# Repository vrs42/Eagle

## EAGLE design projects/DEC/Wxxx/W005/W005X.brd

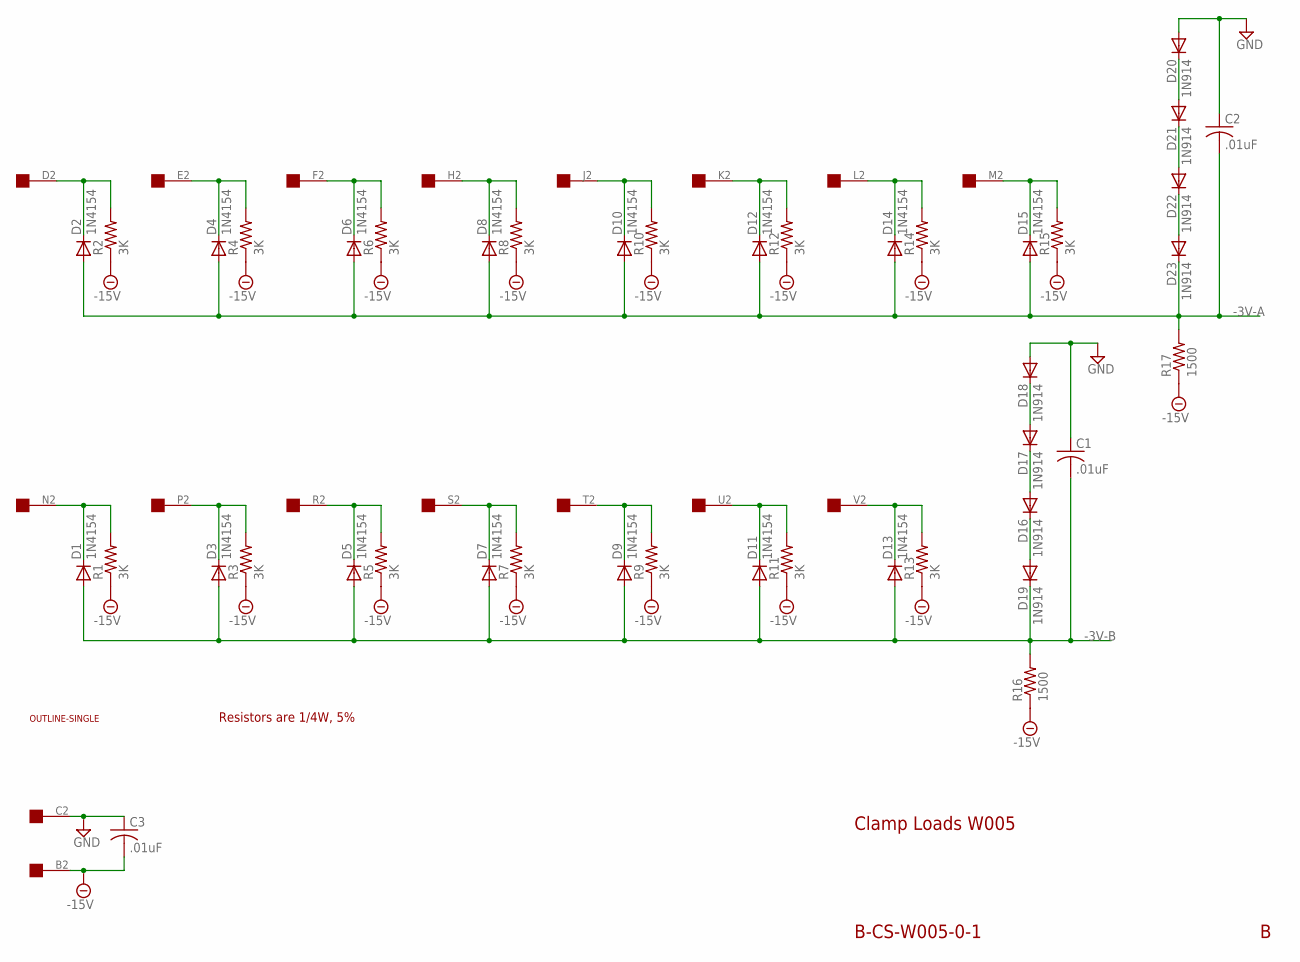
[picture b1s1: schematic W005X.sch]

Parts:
C1, C2, C3: .01uF; C050-025X075
D1, D2, D3, D4, D5, D6, D7, D8, D9, D10, D11, D12, D13, D14, D15: 1N4154; DO35-10
D16, D17, D18, D19, D20, D21, D22, D23: 1N914; DO35-10
R1, R2, R3, R4, R5, R6, R7, R8, R9, R10, R11, R12, R13, R14, R15: 3K; 0207/10
R16, R17: 1500; 0207/10
U$1: OUTLINE-SINGLE; SINGLE
U$2: EDGE-1; EDGE-CON1

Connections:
-3V-A: C2.2, D2.A, D4.A, D6.A, D8.A, D10.A, D12.A, D14.A, D15.A, D23.C, R17.2
-3V-B: C1.2, D1.A, D3.A, D5.A, D7.A, D9.A, D11.A, D13.A, D19.C, R16.2
-15V: C3.2, R1.1, R2.1, R3.1, R4.1, R5.1, R6.1, R7.1, R8.1, R9.1, R10.1, R11.1, R12.1, R13.1, R14.1, R15.1, R16.1, R17.1, U$2.B2
GND: C1.1, C2.1, C3.1, D18.A, D20.A, U$2.C2
unnamed: D22.C, D23.A
unnamed: D2.C, R2.2, U$2.D2
unnamed: D4.C, R4.2, U$2.E2
unnamed: D1.C, R1.2, U$2.N2
unnamed: D3.C, R3.2, U$2.P2
unnamed: D5.C, R5.2, U$2.R2
unnamed: D6.C, R6.2, U$2.F2
unnamed: D7.C, R7.2, U$2.S2
unnamed: D8.C, R8.2, U$2.H2
unnamed: D9.C, R9.2, U$2.T2
unnamed: D10.C, R10.2, U$2.J2
unnamed: D11.C, R11.2, U$2.U2
unnamed: D12.C, R12.2, U$2.K2
unnamed: D13.C, R13.2, U$2.V2
unnamed: D14.C, R14.2, U$2.L2
unnamed: D15.C, R15.2, U$2.M2
unnamed: D17.A, D18.C
unnamed: D16.A, D17.C
unnamed: D16.C, D19.A
unnamed: D20.C, D21.A
unnamed: D21.C, D22.A

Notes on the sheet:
Clamp Loads W005
B-CS-W005-0-1
Resistors are 1/4W, 5%

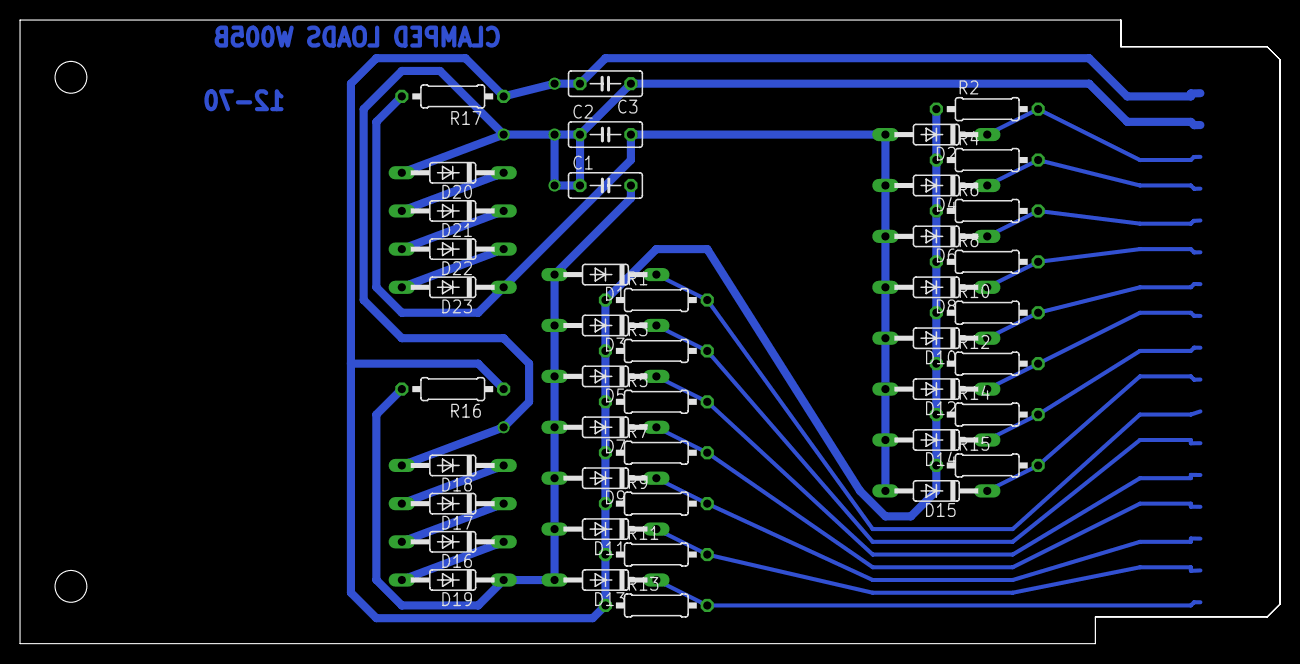
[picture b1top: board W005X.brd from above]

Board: 2 copper layers, 125.7 x 62.2 mm, 45 parts (0 on the bottom side), 25 nets.

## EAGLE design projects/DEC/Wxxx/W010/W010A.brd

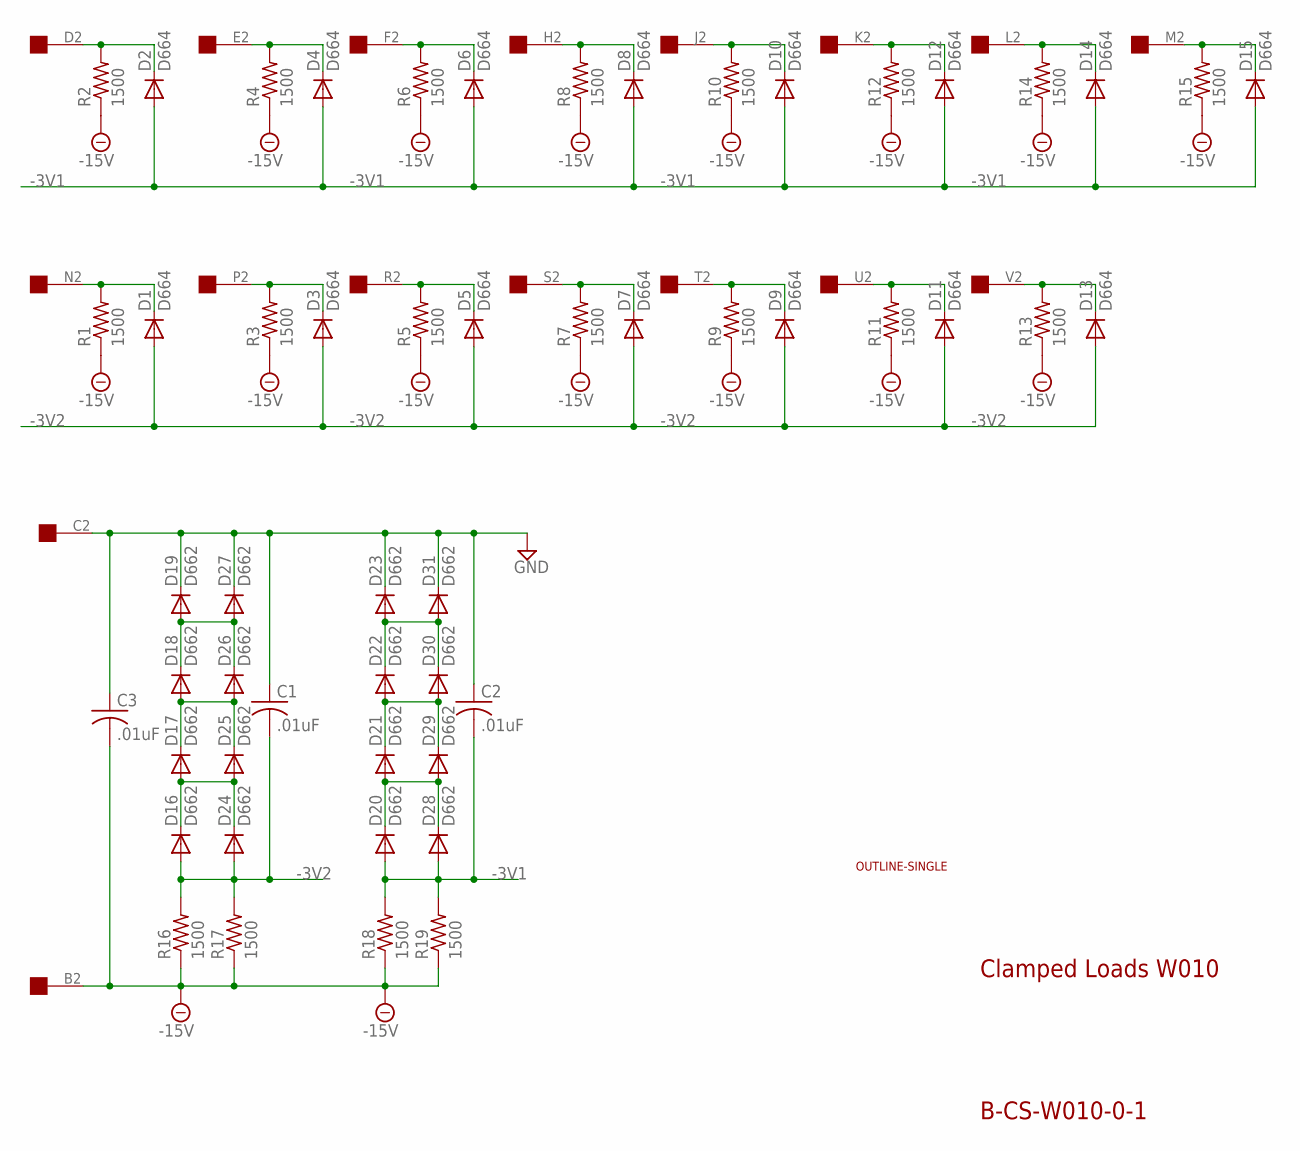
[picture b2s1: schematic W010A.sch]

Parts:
C1, C2, C3: .01uF; C063-025X075
D1, D2, D3, D4, D5, D6, D7, D8, D9, D10, D11, D12, D13, D14, D15: D664; DO35-10
D16, D17, D18, D19, D20, D21, D22, D23, D24, D25, D26, D27, D28, D29, D30, D31: D662; DO35-10
R1, R2, R3, R4, R5, R6, R7, R8, R9, R10, R11, R12, R13, R14, R15, R16, R17, R18, R19: 1500; 0207/10
U$1: EDGE-1; EDGE-CON1
U$2: OUTLINE-SINGLE; SINGLE

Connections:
-3V1: C2.2, D2.A, D4.A, D6.A, D8.A, D10.A, D12.A, D14.A, D15.A, D20.A, D28.A, R18.2, R19.2
-3V2: C1.2, D1.A, D3.A, D5.A, D7.A, D9.A, D11.A, D13.A, D16.A, D24.A, R16.2, R17.2
-15V: C3.2, R1.1, R2.1, R3.1, R4.1, R5.1, R6.1, R7.1, R8.1, R9.1, R10.1, R11.1, R12.1, R13.1, R14.1, R15.1, R16.1, R17.1, R18.1, R19.1, U$1.B2
GND: C1.1, C2.1, C3.1, D19.C, D23.C, D27.C, D31.C, U$1.C2
unnamed: D2.C, R2.2, U$1.D2
unnamed: D4.C, R4.2, U$1.E2
unnamed: D6.C, R6.2, U$1.F2
unnamed: D8.C, R8.2, U$1.H2
unnamed: D10.C, R10.2, U$1.J2
unnamed: D12.C, R12.2, U$1.K2
unnamed: D14.C, R14.2, U$1.L2
unnamed: D15.C, R15.2, U$1.M2
unnamed: D1.C, R1.2, U$1.N2
unnamed: D3.C, R3.2, U$1.P2
unnamed: D5.C, R5.2, U$1.R2
unnamed: D7.C, R7.2, U$1.S2
unnamed: D9.C, R9.2, U$1.T2
unnamed: D11.C, R11.2, U$1.U2
unnamed: D13.C, R13.2, U$1.V2
unnamed: D16.C, D17.A, D24.C, D25.A
unnamed: D17.C, D18.A, D25.C, D26.A
unnamed: D18.C, D19.A, D26.C, D27.A
unnamed: D20.C, D21.A, D28.C, D29.A
unnamed: D21.C, D22.A, D29.C, D30.A
unnamed: D22.C, D23.A, D30.C, D31.A

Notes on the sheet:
Clamped Loads W010
B-CS-W010-0-1

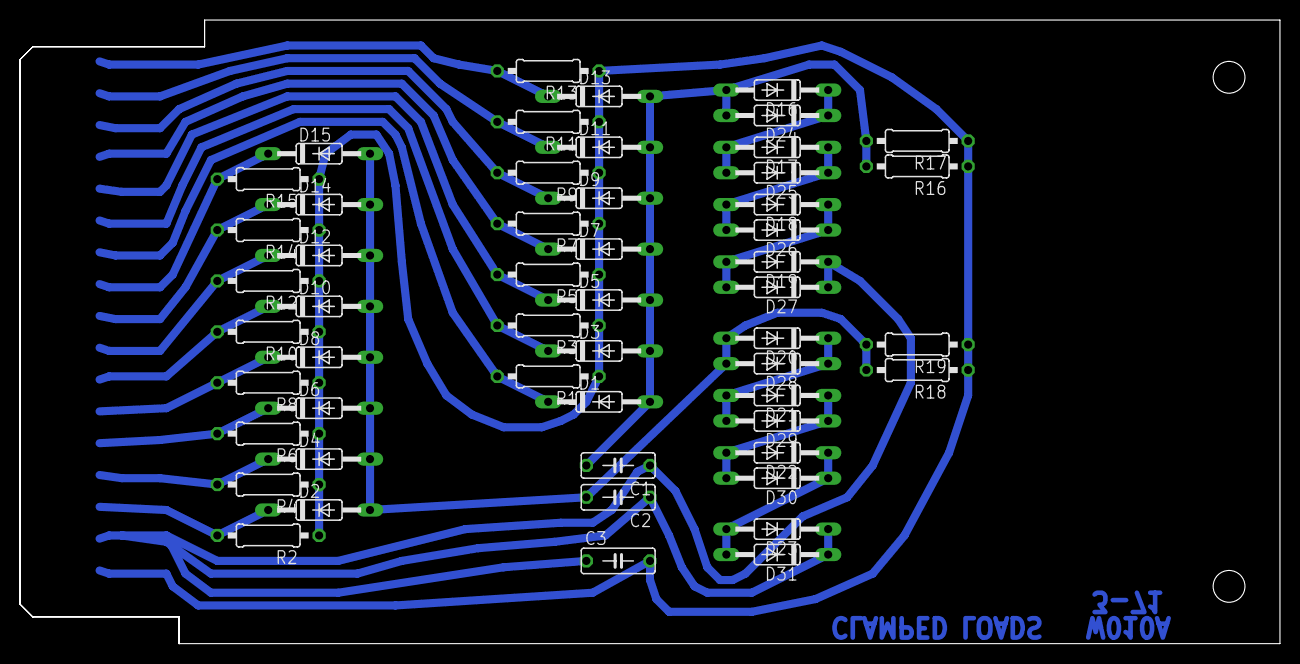
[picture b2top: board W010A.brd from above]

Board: 2 copper layers, 125.7 x 62.2 mm, 55 parts (0 on the bottom side), 25 nets.

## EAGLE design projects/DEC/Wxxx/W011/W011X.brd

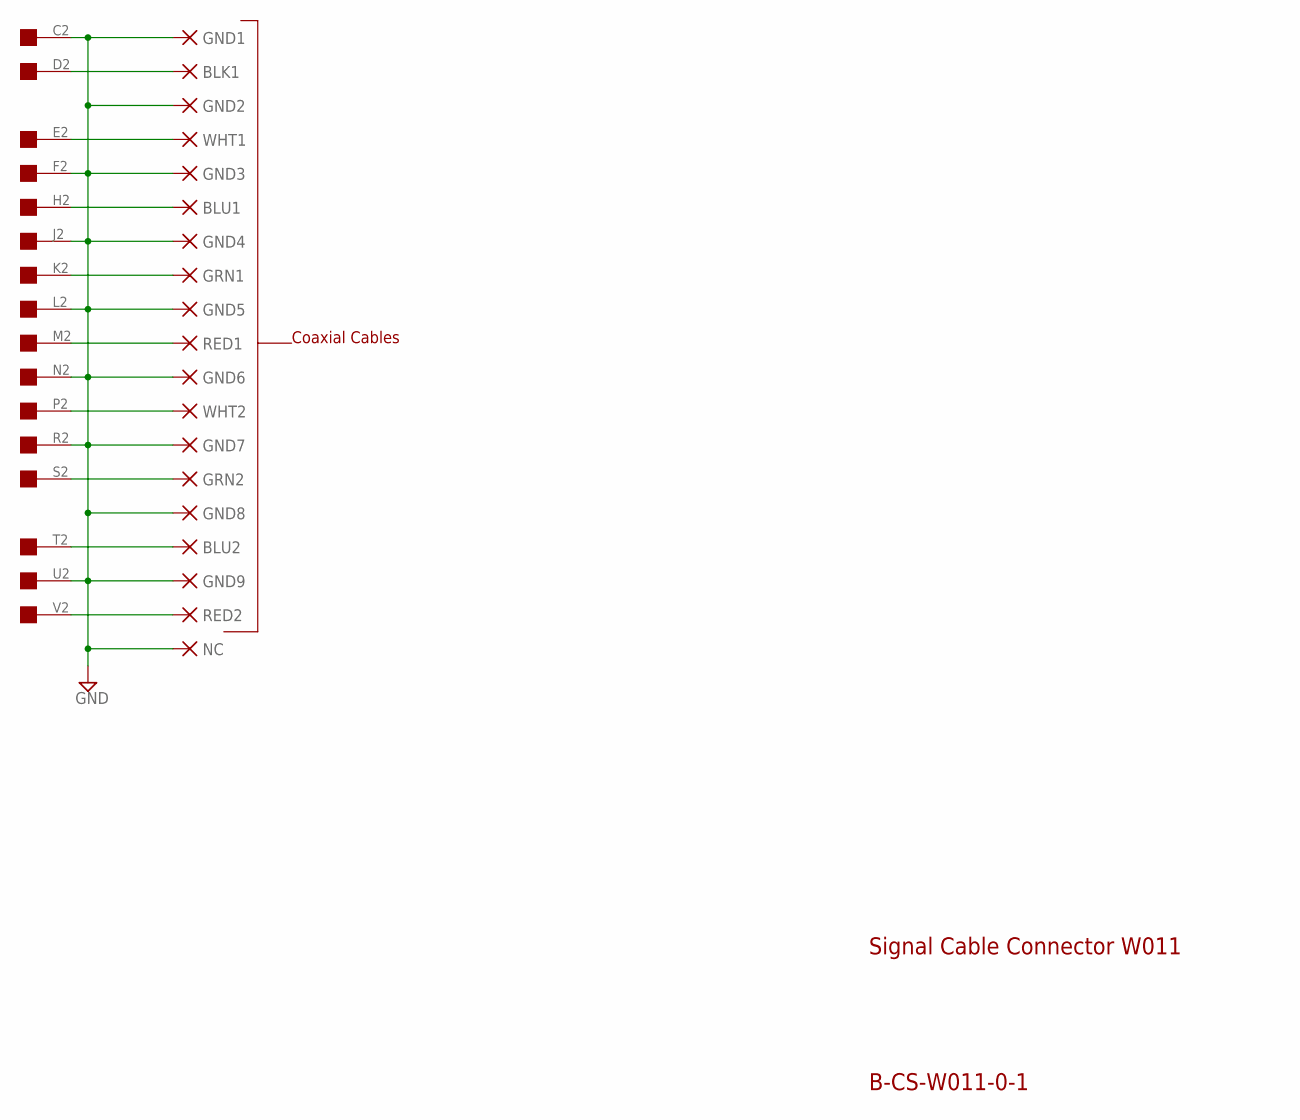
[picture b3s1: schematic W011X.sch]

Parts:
BLK1: PAD-0465; 0465
BLU1, BLU2: PAD-0465; 0465
GND1, GND2, GND3, GND4, GND5, GND6, GND7, GND8, GND9: PAD-0465; 0465
GRN1, GRN2: PAD-0465; 0465
NC: PAD-0465; 0465
RED1, RED2: PAD-0465; 0465
U$2: EDGE-1; EDGE-CON1
WHT1, WHT2: PAD-0465; 0465

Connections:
GND: GND1.P$1, GND2.P$1, GND3.P$1, GND4.P$1, GND5.P$1, GND6.P$1, GND7.P$1, GND8.P$1, GND9.P$1, NC.P$1, U$2.C2, U$2.F2, U$2.J2, U$2.L2, U$2.N2, U$2.R2, U$2.U2
unnamed: U$2.E2, WHT1.P$1
unnamed: BLU1.P$1, U$2.H2
unnamed: GRN1.P$1, U$2.K2
unnamed: RED1.P$1, U$2.M2
unnamed: U$2.P2, WHT2.P$1
unnamed: GRN2.P$1, U$2.S2
unnamed: BLU2.P$1, U$2.T2
unnamed: RED2.P$1, U$2.V2
unnamed: BLK1.P$1, U$2.D2

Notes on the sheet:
Signal Cable Connector W011
B-CS-W011-0-1
Coaxial Cables

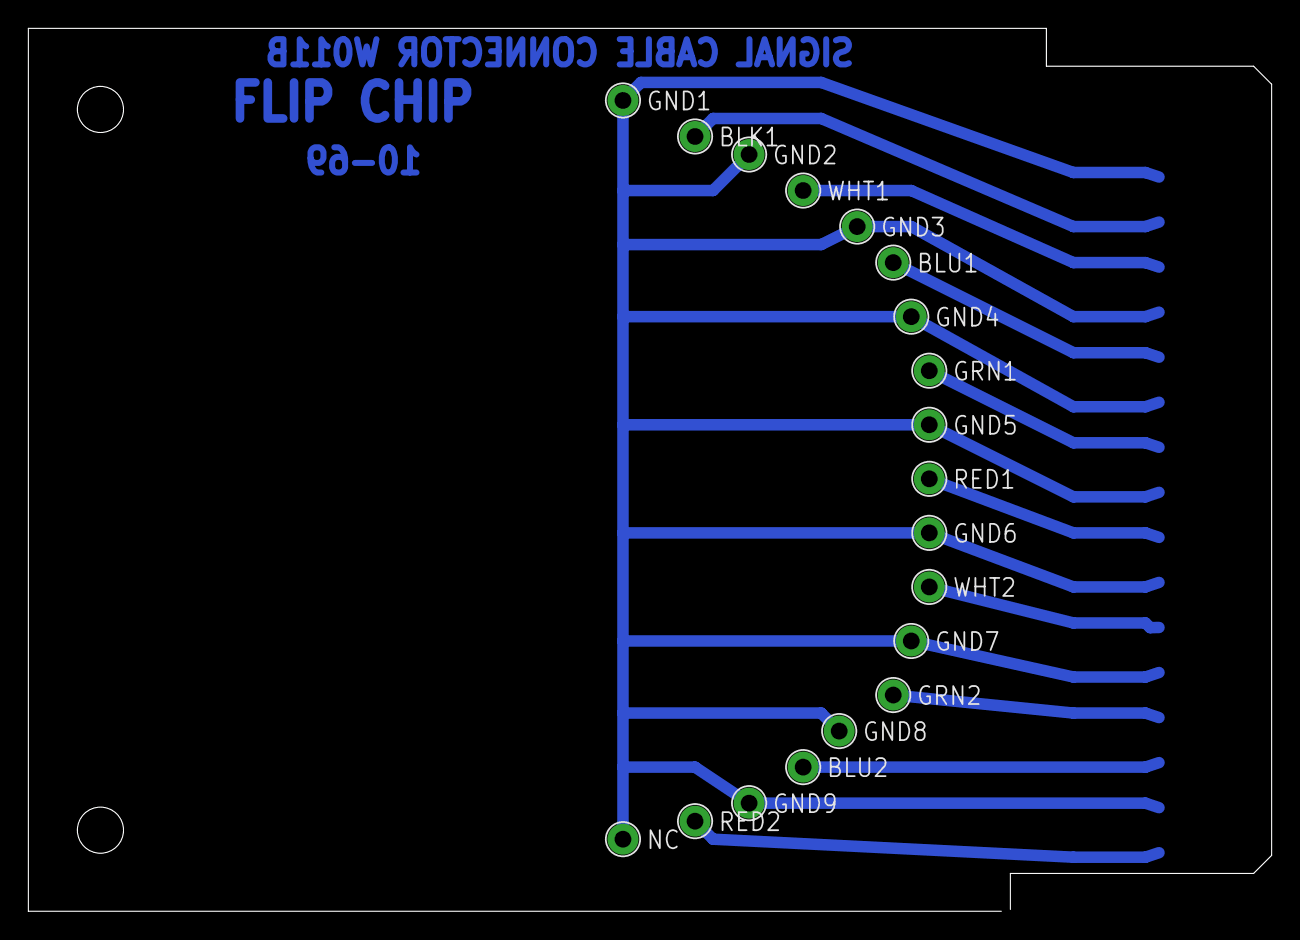
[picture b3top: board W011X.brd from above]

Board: 2 copper layers, 87.6 x 62.2 mm, 20 parts (0 on the bottom side), 10 nets.

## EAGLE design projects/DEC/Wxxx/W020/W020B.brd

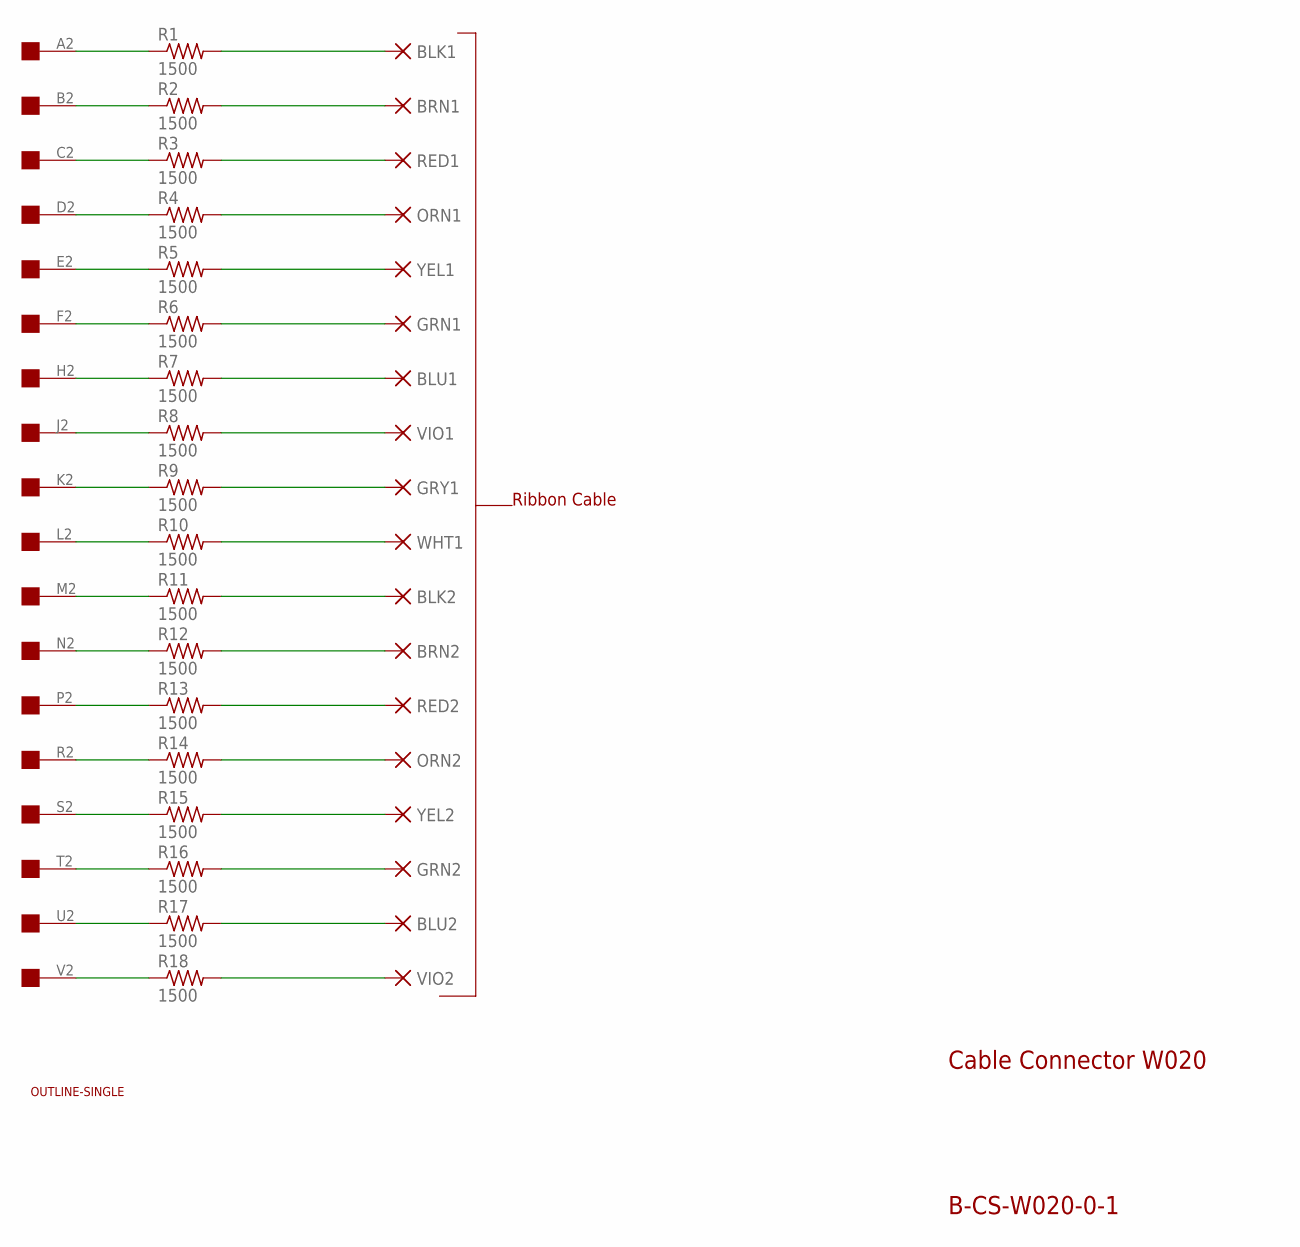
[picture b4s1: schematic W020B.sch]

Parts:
BLK1, BLK2: PAD-0465; 0465
BLU1, BLU2: PAD-0465; 0465
BRN1, BRN2: PAD-0465; 0465
GRN1, GRN2: PAD-0465; 0465
GRY1: PAD-0465; 0465
ORN1, ORN2: PAD-0465; 0465
R1, R2, R3, R4, R5, R6, R7, R8, R9, R10, R11, R12, R13, R14, R15, R16, R17, R18: 1500; 0207/10
RED1, RED2: PAD-0465; 0465
U$1: OUTLINE-SINGLE; SINGLE
U$2: EDGE-1; EDGE-CON1
VIO1, VIO2: PAD-0465; 0465
WHT1: PAD-0465; 0465
YEL1, YEL2: PAD-0465; 0465

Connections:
A2: R1.1, U$2.A2
B2: R2.1, U$2.B2
C2: R3.1, U$2.C2
D2: R4.1, U$2.D2
E2: R5.1, U$2.E2
F2: R6.1, U$2.F2
H2: R7.1, U$2.H2
J2: R8.1, U$2.J2
K2: R9.1, U$2.K2
L2: R10.1, U$2.L2
M2: R11.1, U$2.M2
N2: R12.1, U$2.N2
unnamed: ORN1.P$1, R4.2
unnamed: GRN1.P$1, R6.2
unnamed: R8.2, VIO1.P$1
unnamed: R10.2, WHT1.P$1
unnamed: BRN2.P$1, R12.2
unnamed: ORN2.P$1, R14.2
unnamed: GRN2.P$1, R16.2
unnamed: R18.2, VIO2.P$1
unnamed: BRN1.P$1, R2.2
unnamed: R5.2, YEL1.P$1
unnamed: BLK1.P$1, R1.2
unnamed: R3.2, RED1.P$1
unnamed: BLU1.P$1, R7.2
unnamed: GRY1.P$1, R9.2
unnamed: R13.2, RED2.P$1
unnamed: R15.2, YEL2.P$1
unnamed: BLU2.P$1, R17.2
unnamed: BLK2.P$1, R11.2
P2: R13.1, U$2.P2
R2: R14.1, U$2.R2
S2: R15.1, U$2.S2
T2: R16.1, U$2.T2
U2: R17.1, U$2.U2
V2: R18.1, U$2.V2

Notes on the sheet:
Cable Connector W020
B-CS-W020-0-1
Ribbon Cable

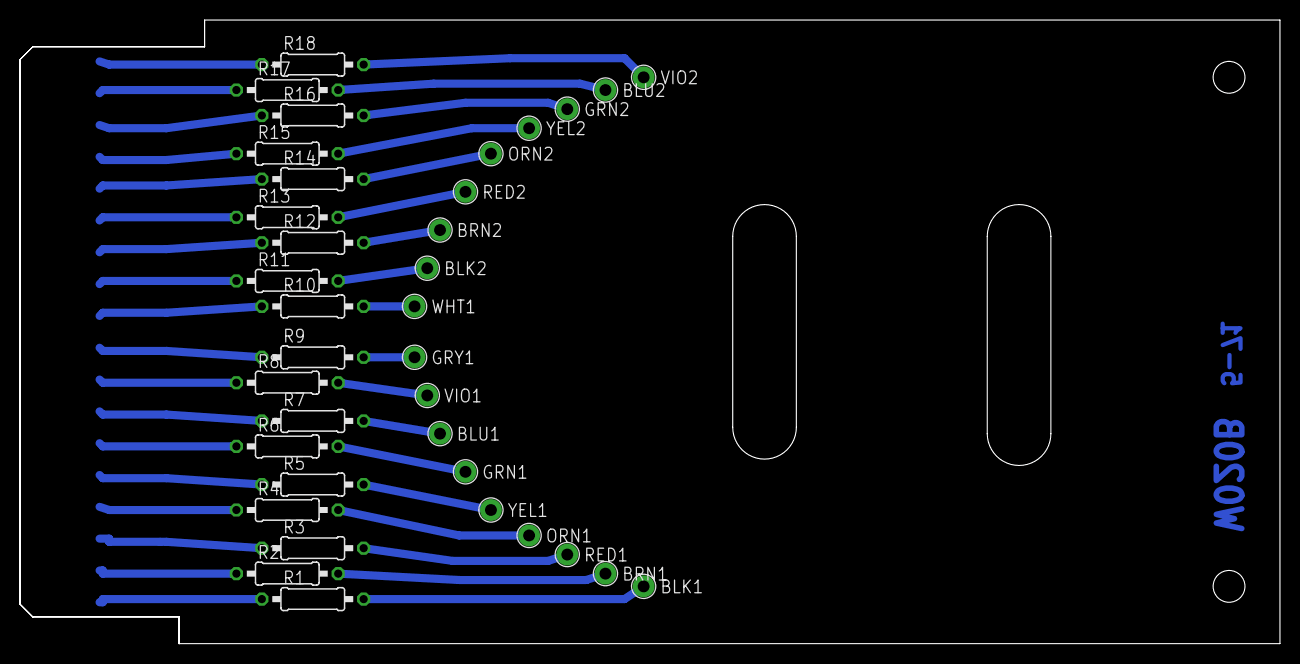
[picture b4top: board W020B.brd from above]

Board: 2 copper layers, 125.7 x 62.2 mm, 38 parts (0 on the bottom side), 36 nets.
